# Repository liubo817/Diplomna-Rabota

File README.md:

# БОБКА - Био-Оптимизатор за Безопасна Костенуркова Атмосфера

## **Описание**
Дипломната работа представя успешната разработка на вградена система, предназначена за наблюдение и управление на терариум за земноводни костенурки. Проектът обхваща иновативен хардуер и софтуер, които съчетават общоприети технологии.

## [Документация](https://docs.google.com/document/d/1n0dCljN07w4FLzlgteggXlk4XJQZPIcb2BojlvGgTRA/edit) ##

## **Създател:**
- **[Любомир Станев](https://github.com/liubo817)**

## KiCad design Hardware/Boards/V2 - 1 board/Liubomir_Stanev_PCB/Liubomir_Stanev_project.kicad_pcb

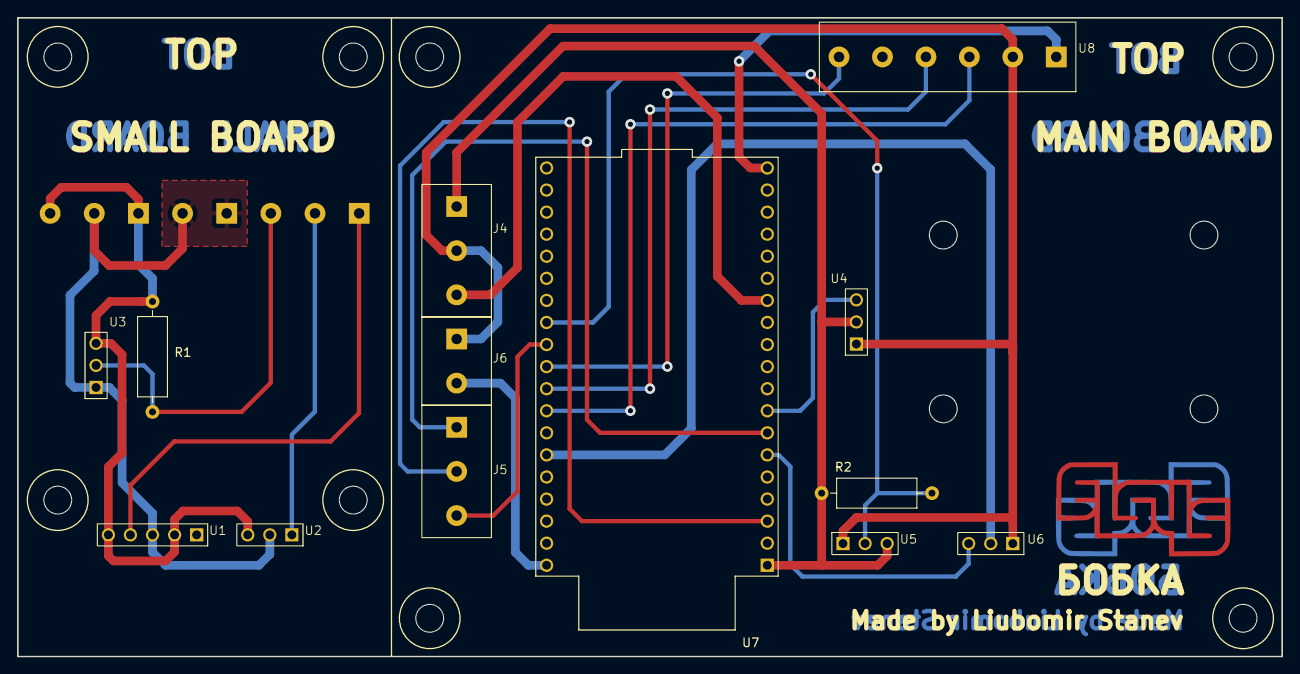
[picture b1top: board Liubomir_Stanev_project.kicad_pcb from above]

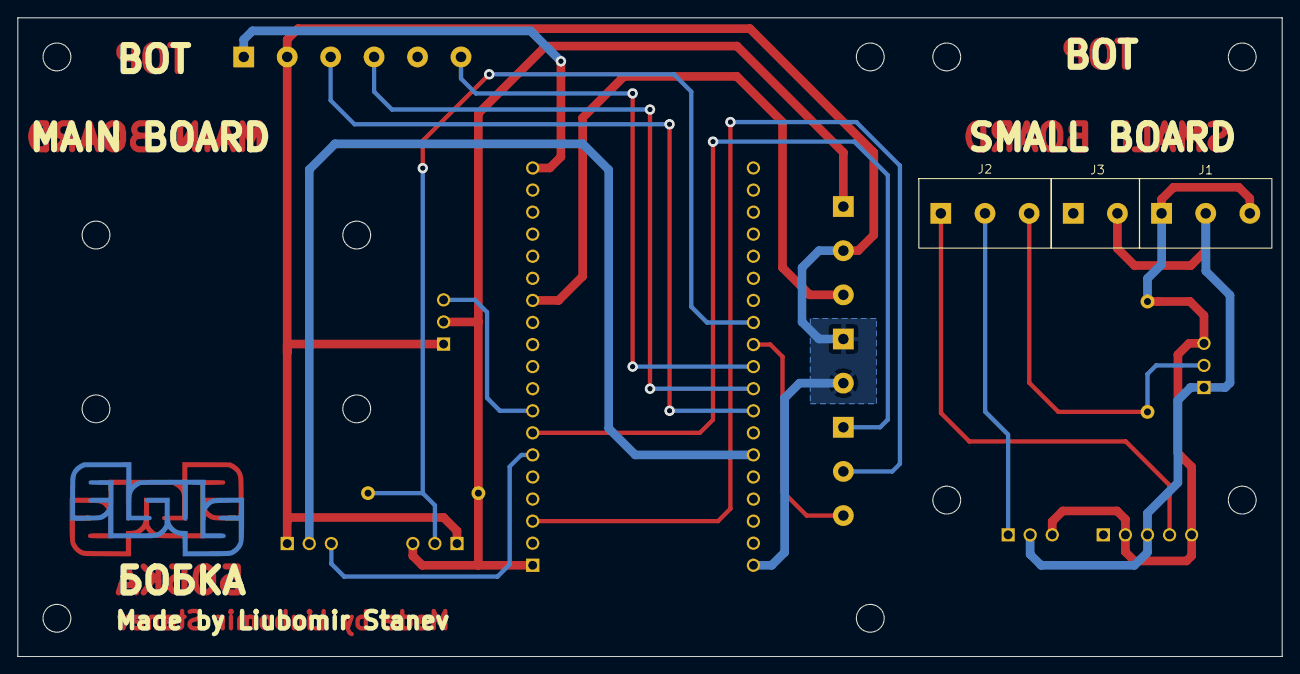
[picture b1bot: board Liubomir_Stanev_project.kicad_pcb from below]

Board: 2 copper layers, 145.5 x 73.5 mm, 16 parts (3 on the bottom side), 19 nets.

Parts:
J1, J2, J4, J5: Conn_01x03_Pin; connector_3p
J3, J6: Conn_01x02_Pin; connector_2p
R1, R2: 2.2k; R_Axial_DIN0309_L9.0mm_D3.2mm_P12.70mm_Horizontal
U1: GY-8511 UV sensor; 5pin_holes
U2: TEMT6000; 3pin_holes
U3: DS18B20-air; 3pin_holes
U4: Turbidity sensor; 3pin_holes
U5: DS18B20-water; 3pin_holes
U6: Water Level Sensor; 3pin_holes
U7: ESP32; MODULE_ESP32-DEVKITC
U8: Relay module; connector_6p

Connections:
+3.3V: J4.1, R2.1, U4.2 (PWR), U5.3 (V_{DD}), U7.1 (+3.3V)
+3V3: J1.1, J1.3, R1.1, U1.2 (3.3V), U1.5 (EN), U2.3 (VCC), U3.3 (V_{DD})
+5V: U7.19 (+5V), U8.1 (VCC)
/air_temp: J2.3, R1.2, U3.2 (DQ)
/air_temp_main: J5.3, U7.30 (GPIO17)
/brightness_out: J2.2, U2.1 (OUT)
/brightness_out_main: J5.2, U7.3 (GPI36)
/relay_brightness_lamp: U7.27 (GPIO19), U8.3 (In1)
/relay_heater: U7.29 (GPIO05), U8.6 (In4)
/relay_uv_lamp: U7.28 (GPIO18), U8.4 (In2)
/turbidity: U4.3 (OUT), U7.8 (GPIO33)
/uv_out: J2.1, U1.4 (OUT)
/uv_out_main: J5.1, U7.7 (GPIO32)
/uv_ref_main: J4.3, U7.13 (GPIO12)
/water_level: U6.3 (OUT), U7.6 (GPI35)
/water_level_power: U6.2 (VCC), U7.25 (GPIO21)
/water_temp: R2.2, U5.2 (DQ), U7.31 (GPIO16)
GND: J4.2, J6.1, J6.2, U4.1 (GND), U5.1 (GND), U6.1 (GND), U7.20 (GND), U8.2 (GND)
GND1: J1.2, J3.1, J3.2, U1.3 (GND), U2.2 (GND), U3.1 (GND)

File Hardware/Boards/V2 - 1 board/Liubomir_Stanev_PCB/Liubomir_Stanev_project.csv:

"Id";"Designator";"Footprint";"Quantity";"Designation";"Supplier and ref";
1;"U7";"MODULE_ESP32-DEVKITC";1;"ESP32";;;
2;"U5";"3pin_holes";1;"DS18B20-water";;;
3;"R1,R2";"R_Axial_DIN0309_L9.0mm_D3.2mm_P12.70mm_Horizontal";2;"2.2k";;;
4;"J4,J5,J1,J2";"connector_3p";4;"Conn_01x03_Pin";;;
5;"U2";"3pin_holes";1;"TEMT6000";;;
6;"U8";"connector_6p";1;"Relay module";;;
7;"J6,J3";"connector_2p";2;"Conn_01x02_Pin";;;
8;"U6";"3pin_holes";1;"Water Level Sensor";;;
9;"U3";"3pin_holes";1;"DS18B20-air";;;
10;"U4";"3pin_holes";1;"Turbidity sensor";;;
11;"U1";"5pin_holes";1;"GY-8511 UV sensor";;;

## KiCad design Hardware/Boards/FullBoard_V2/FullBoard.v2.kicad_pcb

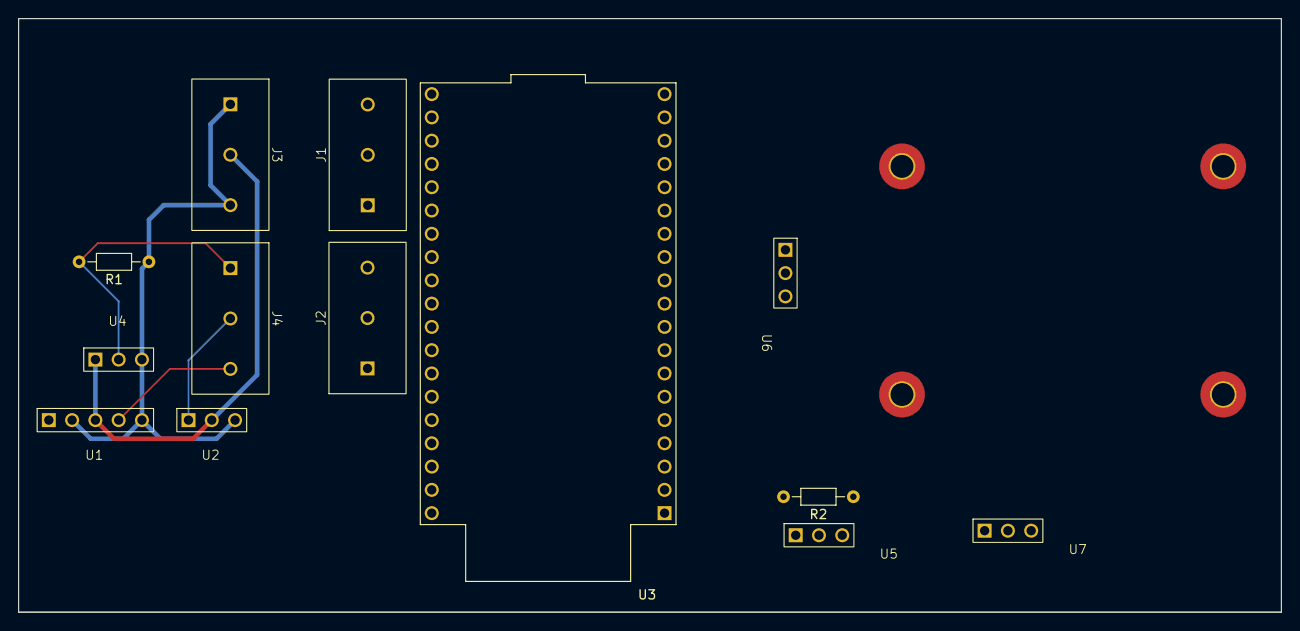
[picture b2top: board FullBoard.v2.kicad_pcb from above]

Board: 2 copper layers, 137.8 x 64.8 mm, 14 parts (0 on the bottom side), 15 nets.

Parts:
J1, J2, J3, J4: Conn_01x03_Pin; connector_3p
K1: Relay_SPDT; Relay
R1, R2: 2.2k; R_Axial_DIN0204_L3.6mm_D1.6mm_P7.62mm_Horizontal
U1: GY-8511 UV sensor; 5pin_holes
U2: TEMT6000; 3pin_holes
U3: MODULE_ESP32-DEVKITC
U4: DS18B20-air; DS18B20_3dmodel
U5: DS18B20-water; DS18B20_3dmodel
U6: Turbidity sensor; 3pin_holes
U7: Water Level; 3pin_holes

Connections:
+3.3V: J1.1, R2.1, U3.1 (+3.3V), U5.3 (V_{DD}), U6.1 (PWR)
+3V3: J3.1, J3.3, R1.1, U1.2 (3.3V), U1.5 (EN), U2.3 (VCC), U4.3 (V_{DD})
/air_temp: J4.1, R1.2, U4.2 (DQ)
/air_temp_main: J2.1, U3.6 (GPI35)
/brightness_out: J4.2, U2.1 (OUT)
/brightness_out_main: J2.2, U3.3 (GPI36)
/turbidity: U3.8 (GPIO33), U6.3 (OUT)
/uv_out: J4.3, U1.4 (OUT)
/uv_out_main: J2.3, U3.7 (GPIO32)
/uv_ref_main: J1.3, U3.13 (GPIO12)
/water_level: U3.15 (GPIO13), U7.3 (OUT)
/water_level_power: U3.25 (GPIO21), U7.2 (VCC)
/water_temp: R2.2, U3.32 (GPIO04), U5.2 (DQ)
GND: J1.2, U3.20 (GND), U5.1 (GND), U6.2 (GND), U7.1 (GND)
GND1: J3.2, U1.3 (GND), U2.2 (GND), U4.1 (GND)

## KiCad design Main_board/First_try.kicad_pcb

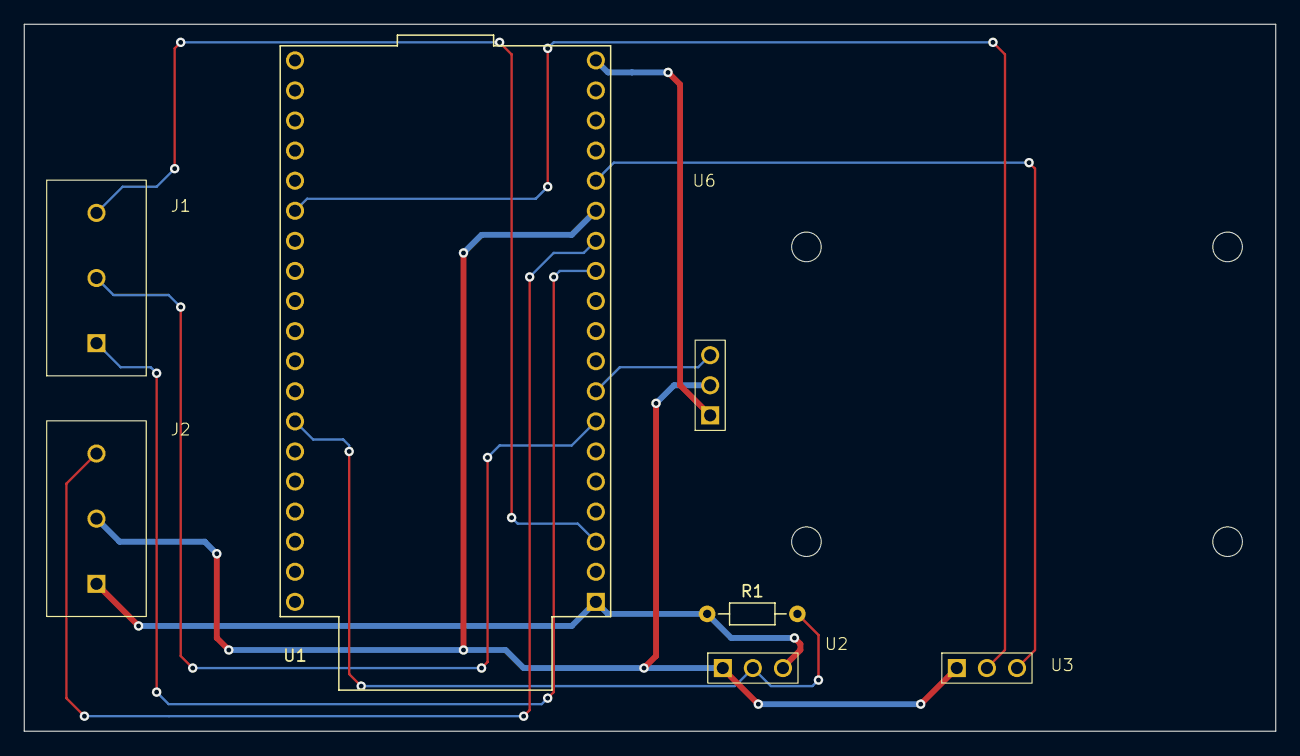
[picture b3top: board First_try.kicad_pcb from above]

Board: 2 copper layers, 105.7 x 59.7 mm, 7 parts (0 on the bottom side), 11 nets.

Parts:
J1, J2: Conn_01x03_Pin; connector_3p
R1: 2.2k; R_Axial_DIN0204_L3.6mm_D1.6mm_P7.62mm_Horizontal
U1: Olimex esp32; MODULE_ESP32-DEVKITC
U2: DS18B20; DS18B20_3dmodel
U3: Water level; DS18B20_3dmodel
U6: SEN0189 Turbidity_sensor; DS18B20_3dmodel

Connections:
+3.3V: J2.1, R1.1, U1.1 (+3.3V), U2.3 (V_{DD})
+5V: U1.19 (+5V), U6.1 (PWR)
/Brightness_out: J1.3, U1.3 (GPIO36)
/Temp_out: J1.1, U1.12 (GPIO14)
/Turbidity_out: U1.8 (GPIO33), U6.3 (OUT)
/UV_out: J1.2, U1.7 (GPIO32)
/UV_ref: J2.3, U1.13 (GPIO12)
/Water_Level_Power: U1.25 (GPIO21), U3.2 (VCC)
/Water_level_out: U1.15 (GPIO13), U3.3 (OUT)
/Water_temp_out: R1.2, U1.32 (GPIO04), U2.2 (DQ)
GND: J2.2, U1.14 (GND), U2.1 (GND), U3.1 (GND), U6.2 (GND)

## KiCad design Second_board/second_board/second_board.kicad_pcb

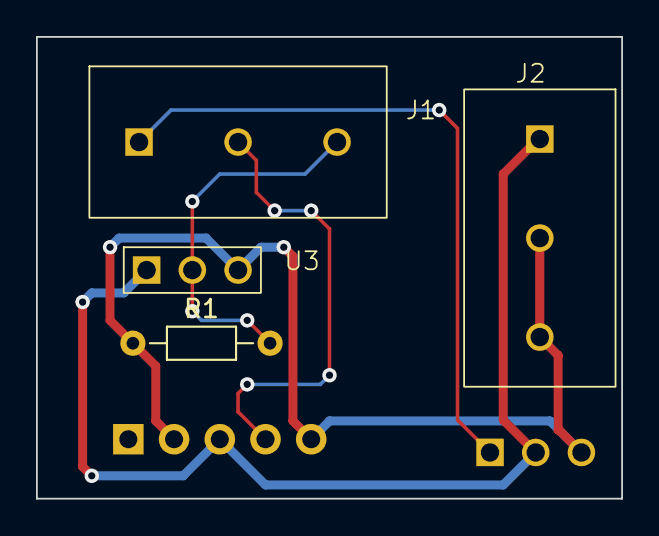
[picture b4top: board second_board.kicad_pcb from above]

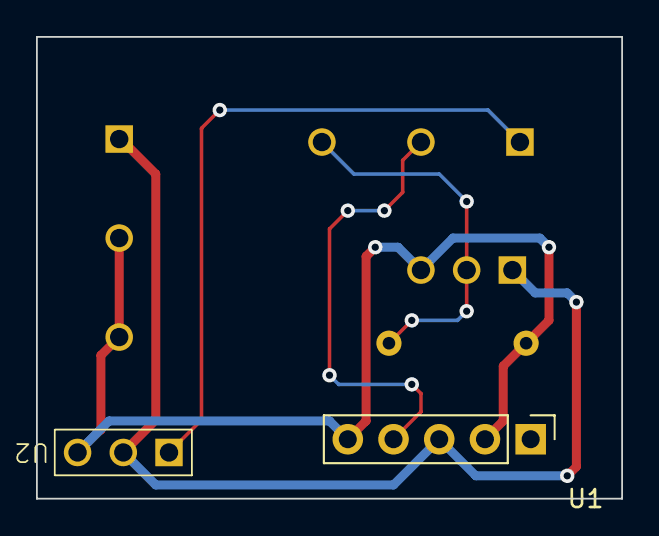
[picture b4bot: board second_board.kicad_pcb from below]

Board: 2 copper layers, 32.5 x 25.7 mm, 6 parts (2 on the bottom side), 5 nets.

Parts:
J1, J2: Conn_01x03_Pin; connector_3p
R1: 2.2k; R_Axial_DIN0204_L3.6mm_D1.6mm_P7.62mm_Horizontal
U1: GY-8511 UV sensor; PinHeader_1x05_P2.54mm_Vertical
U2: TEMT6000; 3pin_holes
U3: DS18B20; DS18B20_3dmodel

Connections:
+3.3V: J2.2, J2.3, R1.1, U1.2 (3.3V), U1.5 (EN), U2.3 (VCC), U3.3 (V_{DD})
/BRIGHTNESS_OUT: J1.1, U2.1 (OUT)
/TEMPERATURE_OUT: J1.3, R1.2, U3.2 (DQ)
/UV_OUT: J1.2, U1.4 (OUT)
GND: J2.1, U1.3 (GND), U2.2 (GND), U3.1 (GND)

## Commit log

2023-11-11 Tested the water level sensor
2023-11-11 Added percantages to the water level sensor as well as working with a LED
2023-11-21 Tested temperature sensor ds18b20 in water - working properly
2023-12-07 Tested the turbidity sensor
2023-12-07 The 3 sensors for the water were tested together
2023-12-12 Semi-working connection between sensor data and a flask web server
2023-12-12 Working connection between Flask webserver and temperarture sensor
2023-12-12 First attempt at trying to display the data on a website
2023-12-19 Displaying data from the temperature sensor on the flask webpage in real time
2023-12-19 Now working in bulgairan timezone
2023-12-19 Removed password and ssid
2023-12-23 Tested the UV sensor
2023-12-24 Every sensor has its own function
2023-12-24 Every sensor on a different graph
2024-01-03 Added schemes
2024-01-07 Made two main folders and added a full scheme
2024-01-09 Tested the logic from the Flask webpage to the ESP32 with LED
2024-01-09 The full board combined
2024-01-10 Second version of the full board
2024-01-18 Almost completed scheme
2024-02-01 Scheme and board completed as well as relay module tested
2024-02-03 PCB almost complete
2024-02-03 Added names on silkscreen and moved some of the connectors
2024-02-03 Combined flask integration and flask to esp32 in the integration code (Working with home WiFi)
2024-02-03 PCB complete
2024-02-03 Fabrication files ready
2024-02-04 Added testing for 3 relays and updated flask app
2024-02-04 Fixed some issues on the board and addded some logic for the turbidity sensor
2024-02-07 Added BOM file
2024-02-10 Some software additions
2024-02-13 Software addditions and auto mode working
2024-02-15 Flask and esp32 updated
2024-02-16 Slight corrections in the software
2024-02-18 Software additions v2
2024-02-20 Added Mechanical details
2024-02-29 Added things for the ReadMe
2024-02-29 Finished ReadMe
